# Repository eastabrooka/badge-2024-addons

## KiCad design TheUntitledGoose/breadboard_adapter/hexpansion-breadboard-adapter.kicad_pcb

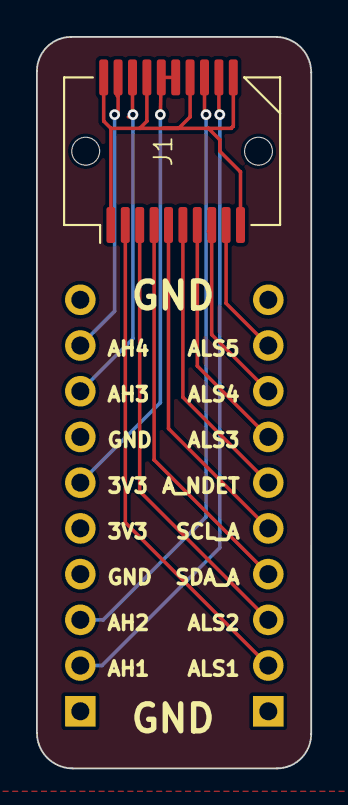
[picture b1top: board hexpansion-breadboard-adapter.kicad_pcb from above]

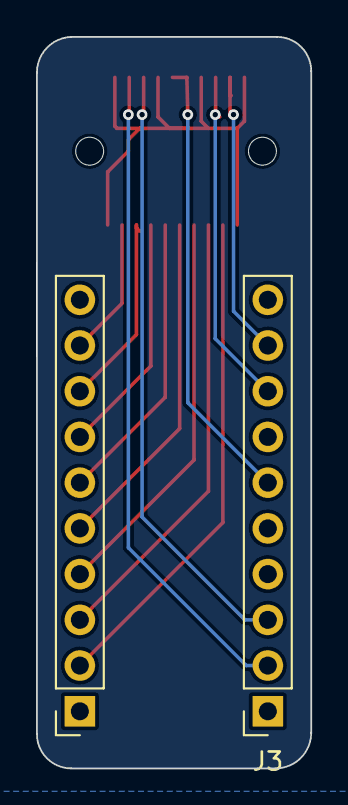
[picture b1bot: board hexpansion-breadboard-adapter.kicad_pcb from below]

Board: 2 copper layers, 15.2 x 40.6 mm, 3 parts (2 on the bottom side), 14 nets.

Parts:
J1: Conn_02x10_Counter_Clockwise; SFP
J2, J3: Conn_01x10_Pin; PinSocket_1x10_P2.54mm_Vertical

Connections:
/AH2: J1.13, J3.3
/AH3: J1.18, J3.8
/AH4: J1.19, J3.9
/DET: J1.6, J2.6
/GND: J1.1, J1.10, J1.11, J1.14, J1.17, J1.20, J2.1, J2.10, J3.1, J3.4, J3.7, J3.10
/HS1: J1.12, J3.2
/LS1: J1.2, J2.2
/LS2: J1.3, J2.3
/LS3: J1.7, J2.7
/LS4: J1.8, J2.8
/LS5: J1.9, J2.9
/PORTA_3V3: J1.15, J1.16, J3.5, J3.6
/SCL: J1.5, J2.5
/SDA: J1.4, J2.4

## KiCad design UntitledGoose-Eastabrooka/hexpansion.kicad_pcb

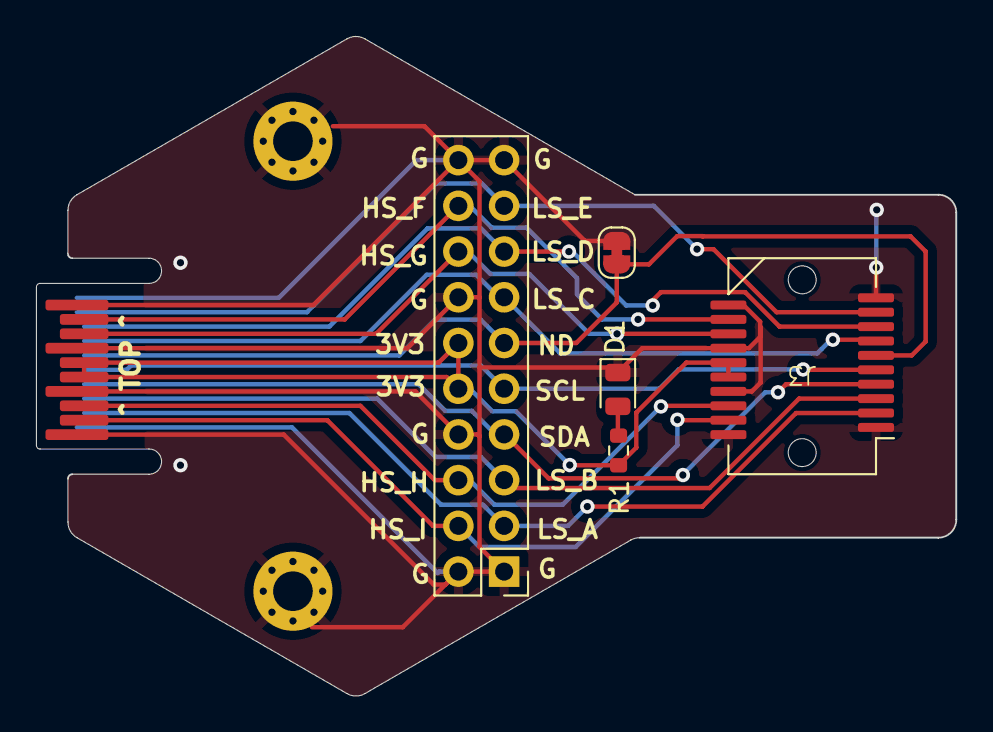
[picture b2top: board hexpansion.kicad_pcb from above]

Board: 2 copper layers, 51.1 x 36.6 mm, 8 parts (0 on the bottom side), 15 nets.

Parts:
D1: LED; LED_0805_2012Metric
H1, H2: MountingHole_Pad; MountingHole_2.2mm_M2_Pad_Via
J1: Hexpansion-Connector; hexpansion-edge-connector
J2: Conn_02x10_Odd_Even; PinHeader_2x10_P2.54mm_Vertical
J3: Conn_02x10_Counter_Clockwise; SFP
JP1: SolderJumper_2_Bridged; SolderJumper-2_P1.3mm_Bridged_RoundedPad1.0x1.5mm
R1: R; R_0603_1608Metric

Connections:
/3V3: J1.15 (3V3), J1.16 (3V3), J2.10, J2.12, J3.15, J3.16, R1.1
/GND: D1.1 (K), H1.1, H2.1, J1.1 (GND), J1.10 (GND), J1.11 (GND), J1.14 (GND), J1.17 (GND), J1.20 (GND), J2.1, J2.2, J2.8, J2.14, J2.19, J2.20, J3.1, J3.10, J3.11, J3.14, J3.17, J3.20, JP1.2 (B)
/HEXP_DET: J1.6 (HEXP_DET), J2.11, J3.6, JP1.1 (A)
/HS_F: J1.12 (HS_F), J2.18, J3.12
/HS_G: J1.13 (HS_G), J2.16, J3.13
/HS_H: J1.18 (HS_H), J2.6, J3.18
/HS_I: J1.19 (HS_I), J2.4, J3.19
/LS_A: J1.2 (LS_A), J2.3, J3.2
/LS_B: J1.3 (LS_B), J2.5, J3.3
/LS_C: J1.7 (LS_C), J2.13, J3.7
/LS_D: J1.8 (LS_D), J2.15, J3.8
/LS_E: J1.9 (LS_E), J2.17, J3.9
/SCL: J1.5 (SCL), J2.9, J3.5
/SDA: J1.4 (SDA), J2.7, J3.4
unnamed: D1.2 (A), R1.2

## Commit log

2024-03-21 Upload Breadboard Breakout
2024-03-21 Stash
2024-06-06 Run Export for Discord.
